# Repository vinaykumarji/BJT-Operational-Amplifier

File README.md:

# BJT Operational Amplifier

### Design, Simulation and Hardware Implementation

A discrete operational amplifier designed using Bipolar Junction
Transistors (BJTs), simulated using LTspice, and implemented
physically using discrete components on a breadboard.

This project explores transistor-level analog circuit design,
including differential amplification, current mirrors, active loads,
Darlington configurations, and closed-loop amplifier applications.

---

## Project Team

- **Vinay Kumar**
- **Kavish**
- **Hardik Sharma**

**Institution:** Indian Institute of Technology Madras  
**Programme:** BS in Electronic Systems  
**Project Date:** September 2026

---

## Objectives

- Design an operational amplifier using discrete BJTs.
- Understand differential amplifiers and current mirrors.
- Implement a PNP transistor active load.
- Develop a Darlington amplification stage.
- Simulate the circuit using LTspice.
- Implement and test the circuit on a breadboard.
- Verify inverting and non-inverting amplifier configurations.
- Compare theoretical and practical results.

---

## Circuit Architecture

The design incorporates the following stages:

1. Differential Input Stage
2. Tail Current Mirror
3. PNP Active Load
4. Darlington Current Mirror
5. Darlington Stage
6. Output Stage

**Power supply:** +12 V and -12 V dual supply.

---

## Tools and Components

- **LTspice** — Circuit simulation and analysis
- **KiCad** — Electronic design tools
- **BJTs** — Transistor-level circuit implementation
- **Function Generator** — Input signal generation
- **Digital Oscilloscope** — Waveform measurement
- **Breadboard** — Physical circuit implementation

---

## Repository Contents

| File | Description |
|---|---|
| `BJT Operational Amplifier.asc` | LTspice operational amplifier schematic |
| `Input Sin wave.jpeg` | Input sinusoidal waveform |
| `Inverting_gain 2.jpeg` | Inverting amplifier experimental waveform |
| `Inverting gain 3.jpeg` | Additional inverting amplifier waveform |
| `non-inverting gain 3.jpeg` | Non-inverting amplifier waveform |
| `breradbord.jpeg` | Physical breadboard implementation |
| `Two-Stage Discrete BJT Operational Amplifier...` | Project report |

---

## Experimental Results

The amplifier was tested using inverting and non-inverting configurations.

| Parameter | Theoretical Gain | Measured Gain |
|---|---:|---:|
| Inverting Amplifier | -2 | Approximately -2.16 |
| Non-Inverting Amplifier | 3 | Approximately 3.22 |

The reported measurements were taken at approximately 1 kHz.

### Inverting Amplifier

The inverting amplifier uses negative feedback to produce an output
that is approximately 180 degrees out of phase with the input.

### Non-Inverting Amplifier

The non-inverting amplifier produces an output that is in phase
with the input signal.

---

## Hardware Implementation

The circuit was assembled using discrete BJTs and passive components
on a breadboard.

The implementation was developed progressively, beginning with the
current mirror and differential pair, followed by the active load
and Darlington stage.

Practical testing highlighted challenges involving transistor
matching, power-supply limitations, temperature variation,
component failures, and differences between simulation and hardware.

---

## Learning Outcomes

- BJT biasing and operating-point analysis
- Differential amplifier design
- Current mirror implementation
- Active-load amplification
- Darlington transistor configurations
- Feedback and closed-loop gain
- LTspice simulation
- Hardware debugging and waveform analysis

---

## Project Documentation

The accompanying project report describes the circuit architecture,
design methodology, practical implementation, experimental results,
and challenges encountered during development.

---

## Disclaimer

This project is an academic prototype intended for learning and
experimental study of analog electronics. It is not presented as
a precision or production-ready operational amplifier.

---

**Developed by Vinay Kumar, Kavish, and Hardik Sharma**  
Indian Institute of Technology Madras

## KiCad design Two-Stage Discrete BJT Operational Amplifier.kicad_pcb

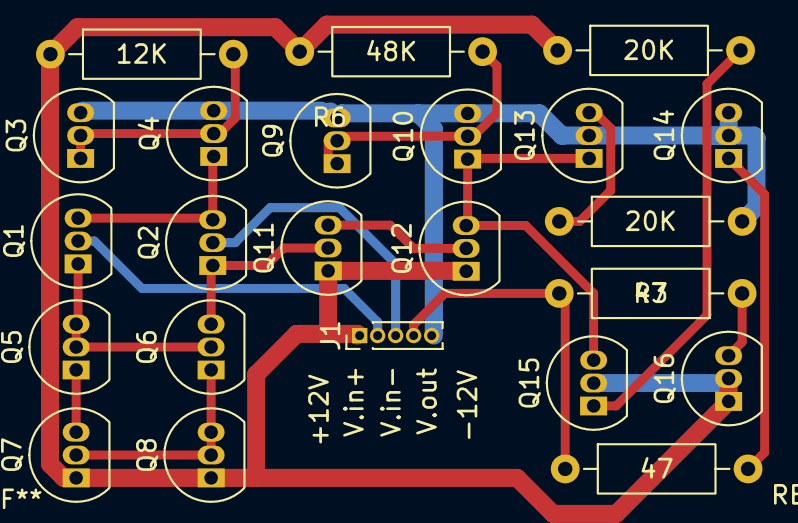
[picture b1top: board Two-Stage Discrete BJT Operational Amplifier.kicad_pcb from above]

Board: 2 copper layers, 23 parts (0 on the bottom side), 18 nets.

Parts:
12K : 12K; R_Axial_DIN0207_L6.3mm_D2.5mm_P10.16mm_Horizontal
20K, 48K: R; R_Axial_DIN0207_L6.3mm_D2.5mm_P10.16mm_Horizontal
J1: Conn_01x05; PinHeader_1x05_P1.00mm_Vertical
Q1, Q2, Q3, Q4, Q9, Q10, Q11, Q12, Q15, Q16: NPN; TO-92_Inline
Q5, Q6, Q7, Q8, Q13, Q14: PNP; TO-92_Inline
R3, R4, R6: R; R_Axial_DIN0207_L6.3mm_D2.5mm_P10.16mm_Horizontal

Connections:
12V: 12K.1, 20K.1, 48K.1, J1.1, Q7.1 (C), Q8.1 (C), Q11.1 (C), Q12.1 (C), Q15.2 (B), Q16.1 (C), Q16.2 (B)
-12V: J1.5, Q3.3 (E), Q4.3 (E), Q9.3 (E), Q10.3 (E), Q13.2 (B), Q14.2 (B), Q14.3 (E), R6.2
-VIN: J1.3, Q2.2 (B)
unnamed: Q1.1 (C), Q5.2 (B), Q5.3 (E), Q6.2 (B)
unnamed: Q1.3 (E), Q2.3 (E), Q4.1 (C)
unnamed: 12K.2, Q3.1 (C), Q3.2 (B), Q4.2 (B)
unnamed: Q5.1 (C), Q7.3 (E)
unnamed: Q6.1 (C), Q7.2 (B), Q8.2 (B), Q8.3 (E)
unnamed: 48K.2, Q9.1 (C), Q9.2 (B), Q10.2 (B)
unnamed: Q10.1 (C), Q12.3 (E), Q13.1 (C), Q15.3 (E)
unnamed: Q2.1 (C), Q6.3 (E), Q11.2 (B)
unnamed: Q11.3 (E), Q12.2 (B)
unnamed: Q13.3 (E), R6.1
unnamed: Q14.1 (C), R4.2
unnamed: 20K.2, Q15.1 (C)
unnamed: Q16.3 (E), R3.1
VIN+: J1.2, Q1.2 (B)
VOUT: J1.4, R3.2, R4.1
